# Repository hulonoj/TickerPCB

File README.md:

# ESP32 14-Segment Ticker Board

A custom-built ESP32-based project using 14-segment hex displays to show real-time data like a clock, stock prices, temperature, and a chess timer.

## What It Does
- Pulls real-time data via Wi-Fi
- Displays info on 8 14-segment displays
- Controlled with 7 physical buttons
- Runs on battery with power management

## Current Modes
- Temperature from 2 i2c sensors
- Real time clock accurate to ~1 second
- Stock Price for any ticker symbol you input
- Chess clock with 5 differet base times and increment

## Photos
Finished Board!

Shows live temperature readings in [temperature testing video](Photos/TempTesting.mp4) and accurate clock in [clock testing video](Photos/ClockTesting.mp4)

Schematic and Layout

## Code Overview
Firmware is written in C++ and manages:
- I2C communication with display drivers
- GPIO input from buttons
- Wi-Fi data fetching
- State switching between display modes

Buttons presses trigger interrupts which are then handled and change state machines to change or move within modes.

## 📚 Notes
I designed and built this project as a personal challenge to deepen my embedded systems skills. The board and code were developed from scratch, and photos illustrate the final product.

## 📝 License
MIT

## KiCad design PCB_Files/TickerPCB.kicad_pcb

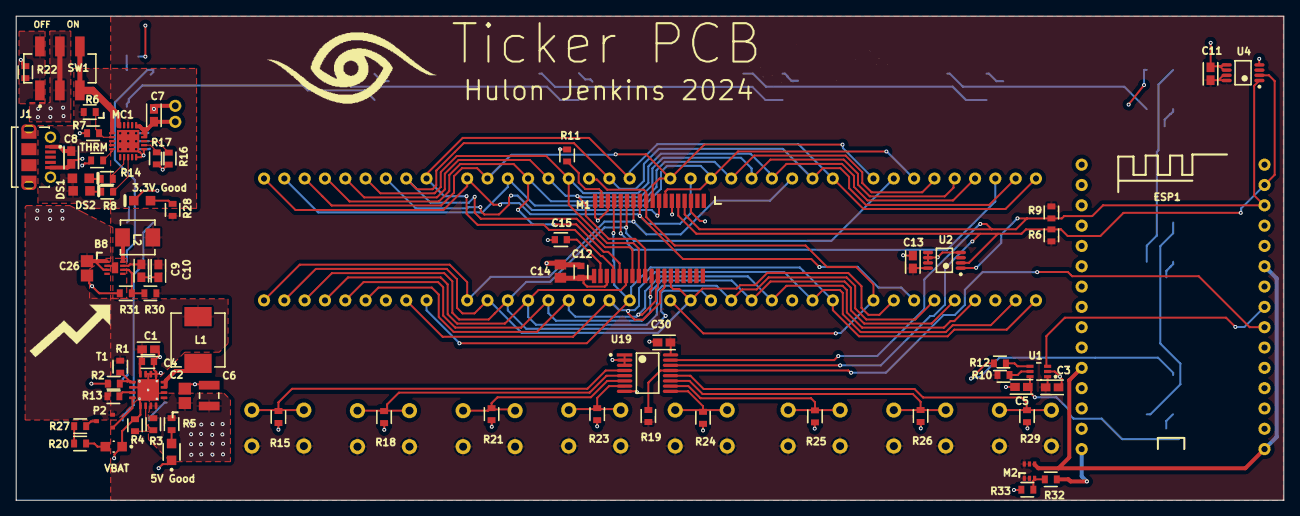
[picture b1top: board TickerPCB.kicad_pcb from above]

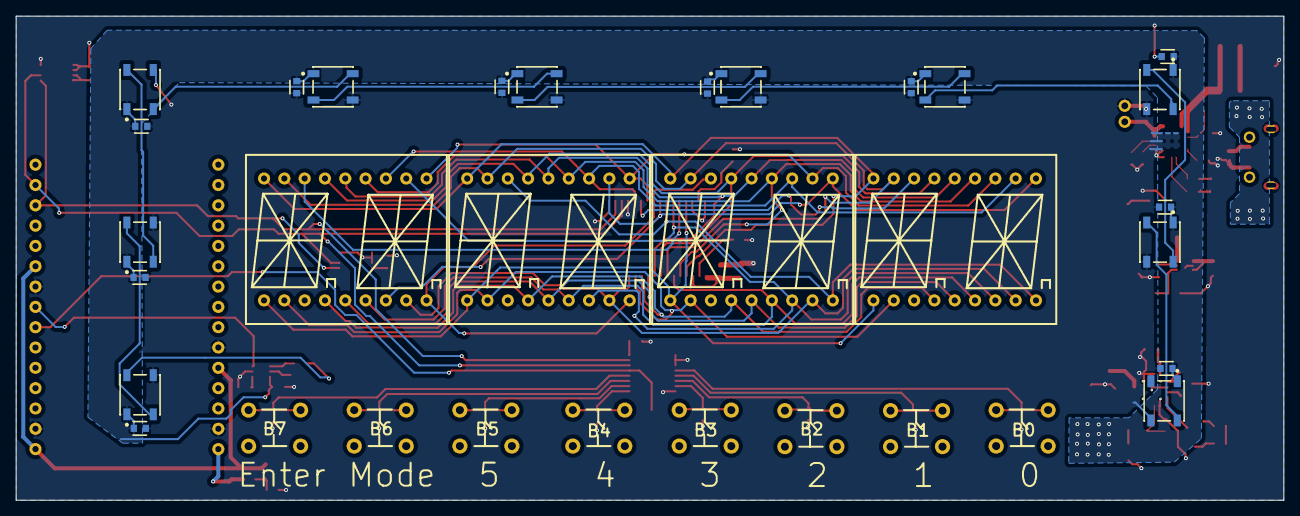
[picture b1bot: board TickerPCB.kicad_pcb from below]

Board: 2 copper layers, 158.5 x 60.5 mm, 104 parts (32 on the bottom side), 76 nets.

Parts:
3.3V Good: HSMG-C170; AVAG-HSMX-C170_V
5V Good: LTST-C170TBKT; FP-LTST-C170TBKT-MFG
B0, B1, B2, B3, B4, B5, B6, B7: Button; PCBCOMPONENT_1
B8: MAX17623
C1, C7, C8, C9, C10: 10uF; FP-GRM188-0_1-e0_2_0_55-IPC_A
C2, C26: 2.2uF; CAPC2013X145X50ML20T25
C3, C5, C11, C13, C30: 1uF; FP-GRM188-0_1-e0_2_0_55-IPC_A
C4: 0.1uF; FP-CC0603-DA-MFG
C6: 100uF; CAPC3225X280X50LL20T25
C12: 100nF 0603; FP-CC0603-DA-MFG
C14: 47uF 0805; CAPC2013X145X45NL20T25
C15: 22pF 0603; FP-CC0603-DA-MFG
C16, C17, C18, C19, C20, C21, C22, C23, C24, C25: 0.1uF 0603; FP-CC0603-DA-MFG
DS1: HSMG-C170; AVAG-HSMX-C170_V
DS2: HSMD-C170; AVAG-HSMX-C170_V
ESP1: ESP8266; PCBComponent_1
H0, H1, H2, H3: LiteOn14Seg; LiteOn 14-Segment Disaply [2]
J1: 105017-0001; USB-MICRO-B_V
L1: 6.8uH; FP-IHLP-2525CZ-FP_2_413x3-MFG
L2: 1uH; FP-IHLP-1616AB-FP_1_8545x-MFG
M1: MAX6955
M2: SI1499dh; PCBComponent_1
MC1: MCP73871
P2: PDTA143Z
R1, R3: 1.87M; FP-CRCW0603-e3-MFG
R2: 340k; FP-CRCW0603-e3-MFG
R4, R13: 200k; FP-CRCW0603-e3-MFG
R5, R20, R27, R28: 200; FP-CRCW0603-e3-MFG
R6: 270k; FP-CRCW0603-e3-MFG
R6#2, R9, R10, R19: 4.7k; FP-CRCW0603-e3-MFG
R7, R17: 100k; FP-CRCW0603-e3-MFG
R8, R14: 470; FP-CRCW0603-e3-MFG
R11: 56k; FP-CRCW0603-e3-MFG
R12: 300; FP-CRCW0603-e3-MFG
R15, R18, R21, R22, R23, R24, R25, R26, R29: 10k; FP-CRCW0603-e3-MFG
R16: 1k; FP-CRCW0603-e3-MFG
R30: 118k; FP-CRCW0603-e3-MFG
R31: 37.4k; FP-CRCW0603-e3-MFG
R32: 3.9k; FP-CRCW0603-e3-MFG
R33: 6.34k; FP-CRCW0603-e3-MFG
SW1: JS202011SCQN; FP-JS202011SCQN-MFG
T1: TPS61090; TPS61090RSAR
THRM: 16k; FP-CRCW0603-e3-MFG
U1: 3.3V-5V Level Shifter; FP-DCK0006A-MFG
U2, U4: MCP9808-E/MS; MCHP-MSOP-MS8_L
U5, U6, U7, U8, U9, U10, U11, U12, U13, U14: NeoPixel1655; ADA-RGB-1655_V
U19: TCA9534PWR; FP-PW0016A-IPC_A
VBAT: HSMS-C170; FP-HSMS-C170-MFG

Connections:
3.3vDATA: ESP1.23, U1.3
5vDATA: R12.2, U1.4
+5: C2.2, C5.1, C6.2, C16.1, C17.1, C18.1, C19.1, C20.1, C21.1, C22.1, C23.1, C24.1, C25.1, R3.2, R5.1, T1.1, T1.15, T1.16, U1.6, U5.1, U6.1, U7.1, U8.1, U9.1, U10.1, U11.1, U12.1, U13.1, U14.1
Button0: B0.2, R15.2, U19.4
Button1: B1.2, R18.2, U19.5
Button2: B2.2, R21.2, U19.6
Button3: B3.2, R23.2, U19.7
Button4: B4.2, R24.2, U19.9
Button5: B5.2, R25.2, U19.10
Button6: B6.2, R26.2, U19.11
Button7: B7.2, R29.2, U19.12
ButtonInt: ESP1.22, R19.1, U19.13
EN: R13.1, T1.11
ESP3.3: ESP1.5, ESP1.16, ESP1.25, M2.S
ESPVIN: ESP1.1, R32.2
FB: R3.1, R4.2, T1.14
GND: 3.3V Good.2, 5V Good.1, B8.2, B8.EP, C1.2, C2.1, C3.2, C4.2, C5.2, C6.1, C7.2, C8.2, C9.2, C10.2, C11.2, C12.2, C13.2, C14.1, C15.2, C16.2, C17.2, C18.2, C19.2, C20.2, C21.2, C22.2, C23.2, C24.2, C25.2, C26.1, C30.2, ESP1.2, ESP1.6, ESP1.17, ESP1.24, J1.5, M1.3, M1.6, M1.16, M1.18, MC1.10, MC1.11, MC1.25, MC1.EP, R2.1, R4.1, R7.1, R11.1, R15.1, R16.1, R17.1, R18.1, R21.1, R22.2, R23.1, R24.1, R25.1, R26.1, R29.1, R31.2, R33.1, T1.5, T1.6, T1.7, T1.10, T1.13, THRM.1, U1.2, U2.4, U2.5, U2.6, U2.7, U4.4, U4.5, U4.6, U5.3, U6.3, U7.3, U8.3, U9.3, U10.3, U11.3, U12.3, U13.3, U14.3, U19.1, U19.2, U19.3, U19.8, VBAT.1
LBI: R1.1, R2.2, T1.9
LBO: P2.1, T1.12
NetB8_6: B8.6, R30.2, R31.1
NetB8_8: B8.8, L2.1
NetC15_1: C15.1, M1.20
NetD1_2: 5V Good.2, R5.2
NetD2_2: R20.1, VBAT.2
NetDS1_2: DS1.2, R14.2
NetDS2_2: DS2.2, R8.1
NetDS3_1: 3.3V Good.1, R28.1
NetM1_17: M1.17, R11.2
NetM2_G: M2.G, R32.1, R33.2
NetMC1_7: MC1.7, R14.1
NetMC1_8: MC1.8, R8.2
NetMC1_12: MC1.12, R17.2
NetMC1_13: MC1.13, R16.2
NetP2_3: P2.3, R27.2
NetR10_2: R10.2, U1.5
NetR12_1: R12.1, U5.4
NetR20_2: R20.2, R27.1
NetR22_1: R22.1, SW1.1, SW1.4
NetU5_2: U5.2, U6.4
NetU6_2: U6.2, U7.4
NetU7_2: U7.2, U8.4
NetU8_2: U8.2, U9.4
NetU9_2: U9.2, U10.4
NetU10_2: U10.2, U11.4
NetU11_2: U11.2, U12.4
NetU12_2: U12.2, U13.4
NetU13_2: U13.2, U14.4
O0: H0.11, H1.12, H2.12, H3.12, M1.7
O1: H0.16, M1.8
O2: H0.12, H1.11, H2.10, H3.10, M1.9
O3: H1.16, H2.9, H3.9, M1.10
O4: H0.10, H1.10, H2.11, H3.7, M1.11
O5: H0.9, H1.9, H2.16, M1.12
O6: H0.7, H1.7, H2.7, H3.11, M1.13
O7: H3.16, M1.14
O8: H0.1, H1.1, H2.1, H3.1, M1.15
O9: H0.18, H1.18, H2.18, H3.18, M1.22
O10: H0.13, H1.13, H2.13, H3.13, M1.23
O11: H0.6, H1.6, H2.6, H3.6, M1.24
O12: H0.17, H1.17, H2.17, H3.17, M1.25
O13: H0.15, H1.15, H2.15, H3.15, M1.26
O14: H0.14, H1.14, H2.14, H3.14, M1.27
O15: H0.5, H1.5, H2.5, H3.5, M1.28
O16: H0.4, H1.4, H2.4, H3.4, M1.29
O17: H0.2, H1.2, H2.2, H3.2, M1.30
O18: H0.8, H1.8, H2.8, H3.8, M1.31
OUT: MC1.1, MC1.20, SW1.3, SW1.6
SCL: ESP1.29, M1.5, R6#2.1, U2.2, U4.2, U19.14
SDA: ESP1.28, M1.4, R9.1, U2.1, U4.1, U19.15
SW: L1.2, T1.3, T1.4
THERM: MC1.5, THRM.2
VBAT: B8.1, B8.3, C1.1, C4.1, C26.2, L1.1, P2.2, R1.2, R13.2, SW1.2, SW1.5, T1.8
VBUS: C8.1, DS1.1, DS2.1, J1.1, MC1.3, MC1.4, MC1.9, MC1.17, MC1.18, MC1.19, R6.2
VCC: B0.1, B1.1, B2.1, B3.1, B4.1, B5.1, B6.1, B7.1, B8.7, C3.1, C9.1, C10.1, C11.1, C12.1, C13.1, C14.2, C30.1, L2.2, M1.19, M1.21, M2.D, R6#2.2, R9.2, R10.1, R19.2, R28.2, R30.1, U1.1, U2.8, U4.7, U4.8, U19.16
VLIPO: C7.1, MC1.14, MC1.15, MC1.16
VPCC: MC1.2, R6.1, R7.2

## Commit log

2025-05-23 Add photos and videos
2025-05-23 make video size smaller
2025-05-26 Update readme with modes
2025-05-27 Add code, schematics, layout
2025-05-27 readme update with new png
2025-05-28 add more clock features, update readme
2025-05-29 photo resize
2026-01-23 Clean up schematic
2026-01-23 Revert gpio test change
2026-01-24 finish cleaning up schematic
2026-01-25 Fix Stock API, bug fix clock state
2026-01-29 varda presentation
2026-01-31 Resolve stock bug, latest presentation
2026-02-11 wip: Add neopixel writing
2026-02-17 Make wifi connection non-blocking. Make neopixel animations colored.
